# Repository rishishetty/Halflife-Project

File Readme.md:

This is Week1 project of hacklife :
Starbie Project design has been completed in Kicad
with Schematic drawings
PCB update from schematic
PCB routingEdge cuts
All gerber files and Drill files are generated

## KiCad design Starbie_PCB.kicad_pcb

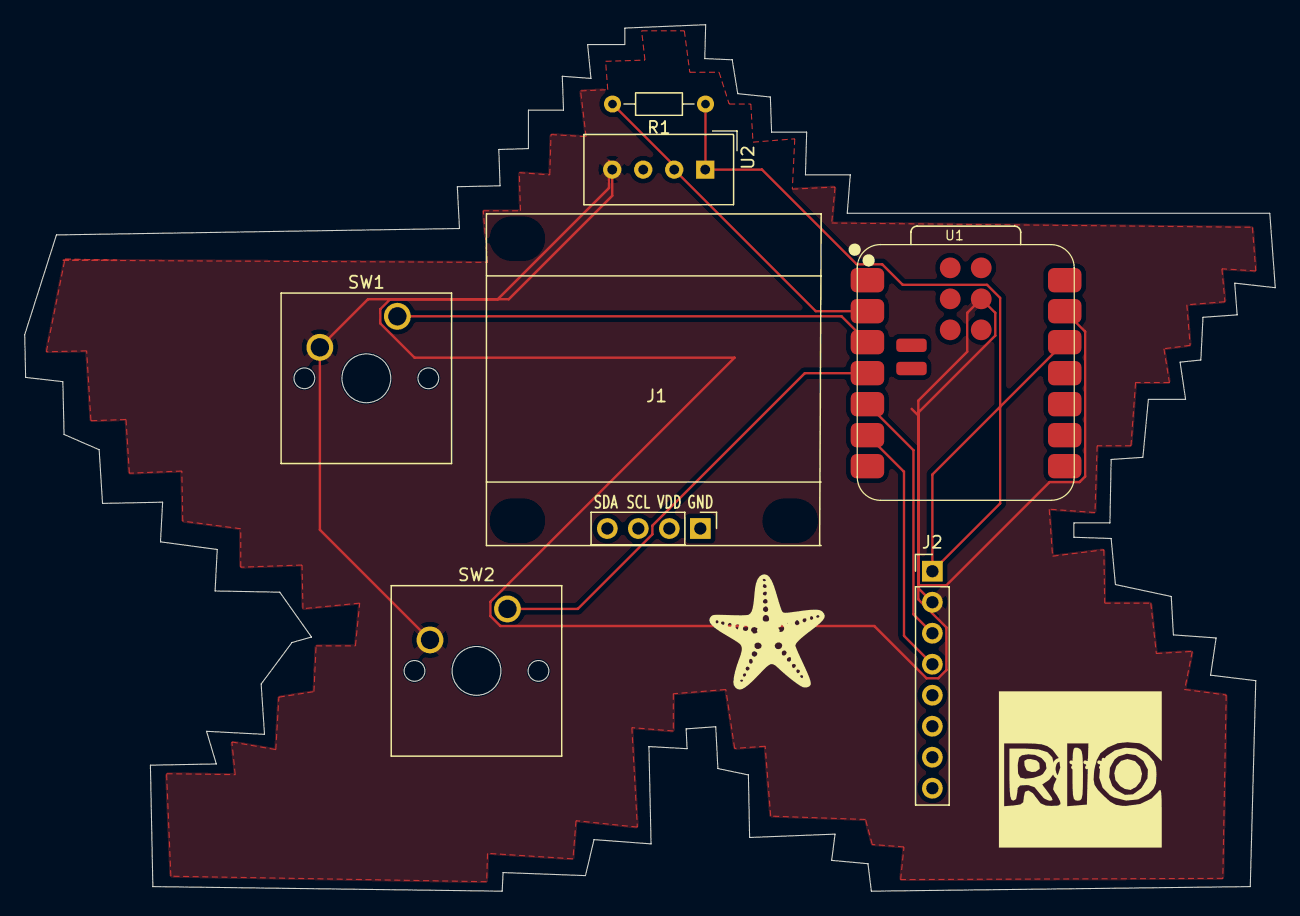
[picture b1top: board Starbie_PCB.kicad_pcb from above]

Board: 2 copper layers, 102.5 x 71.0 mm, 7 parts (0 on the bottom side), 7 nets.

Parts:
J1: Conn_01x04_Pin; Display_128x64_096_I2C
J2: Conn_01x08_Pin; PinHeader_1x08_P2.54mm_Vertical
R1: 10K; R_Axial_DIN0204_L3.6mm_D1.6mm_P7.62mm_Horizontal
SW1, SW2: SW_Push; SW_Cherry_MX_1.00u_PCB
U1: XIAO-ESP32-C3-SMD
U2: DHT11; Aosong_DHT11_5.5x12.0_P2.54mm

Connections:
+3.3V: J2.1, R1.1, U1.12 (3V3_OUT), U2.1 (VDD)
/DHT11 DATA: R1.2, U1.2 (D1), U2.2 (DATA)
/GPIO2: SW1.1, U1.3 (D2)
/GPIO3: SW2.1, U1.4 (D3)
/SCL: J2.3, U1.5 (D4)
/SDA: J2.4, U1.6 (D5)
GND: J2.2, SW1.2, SW2.2, U1.13 (GND), U1.18 (GND), U2.4 (GND)
